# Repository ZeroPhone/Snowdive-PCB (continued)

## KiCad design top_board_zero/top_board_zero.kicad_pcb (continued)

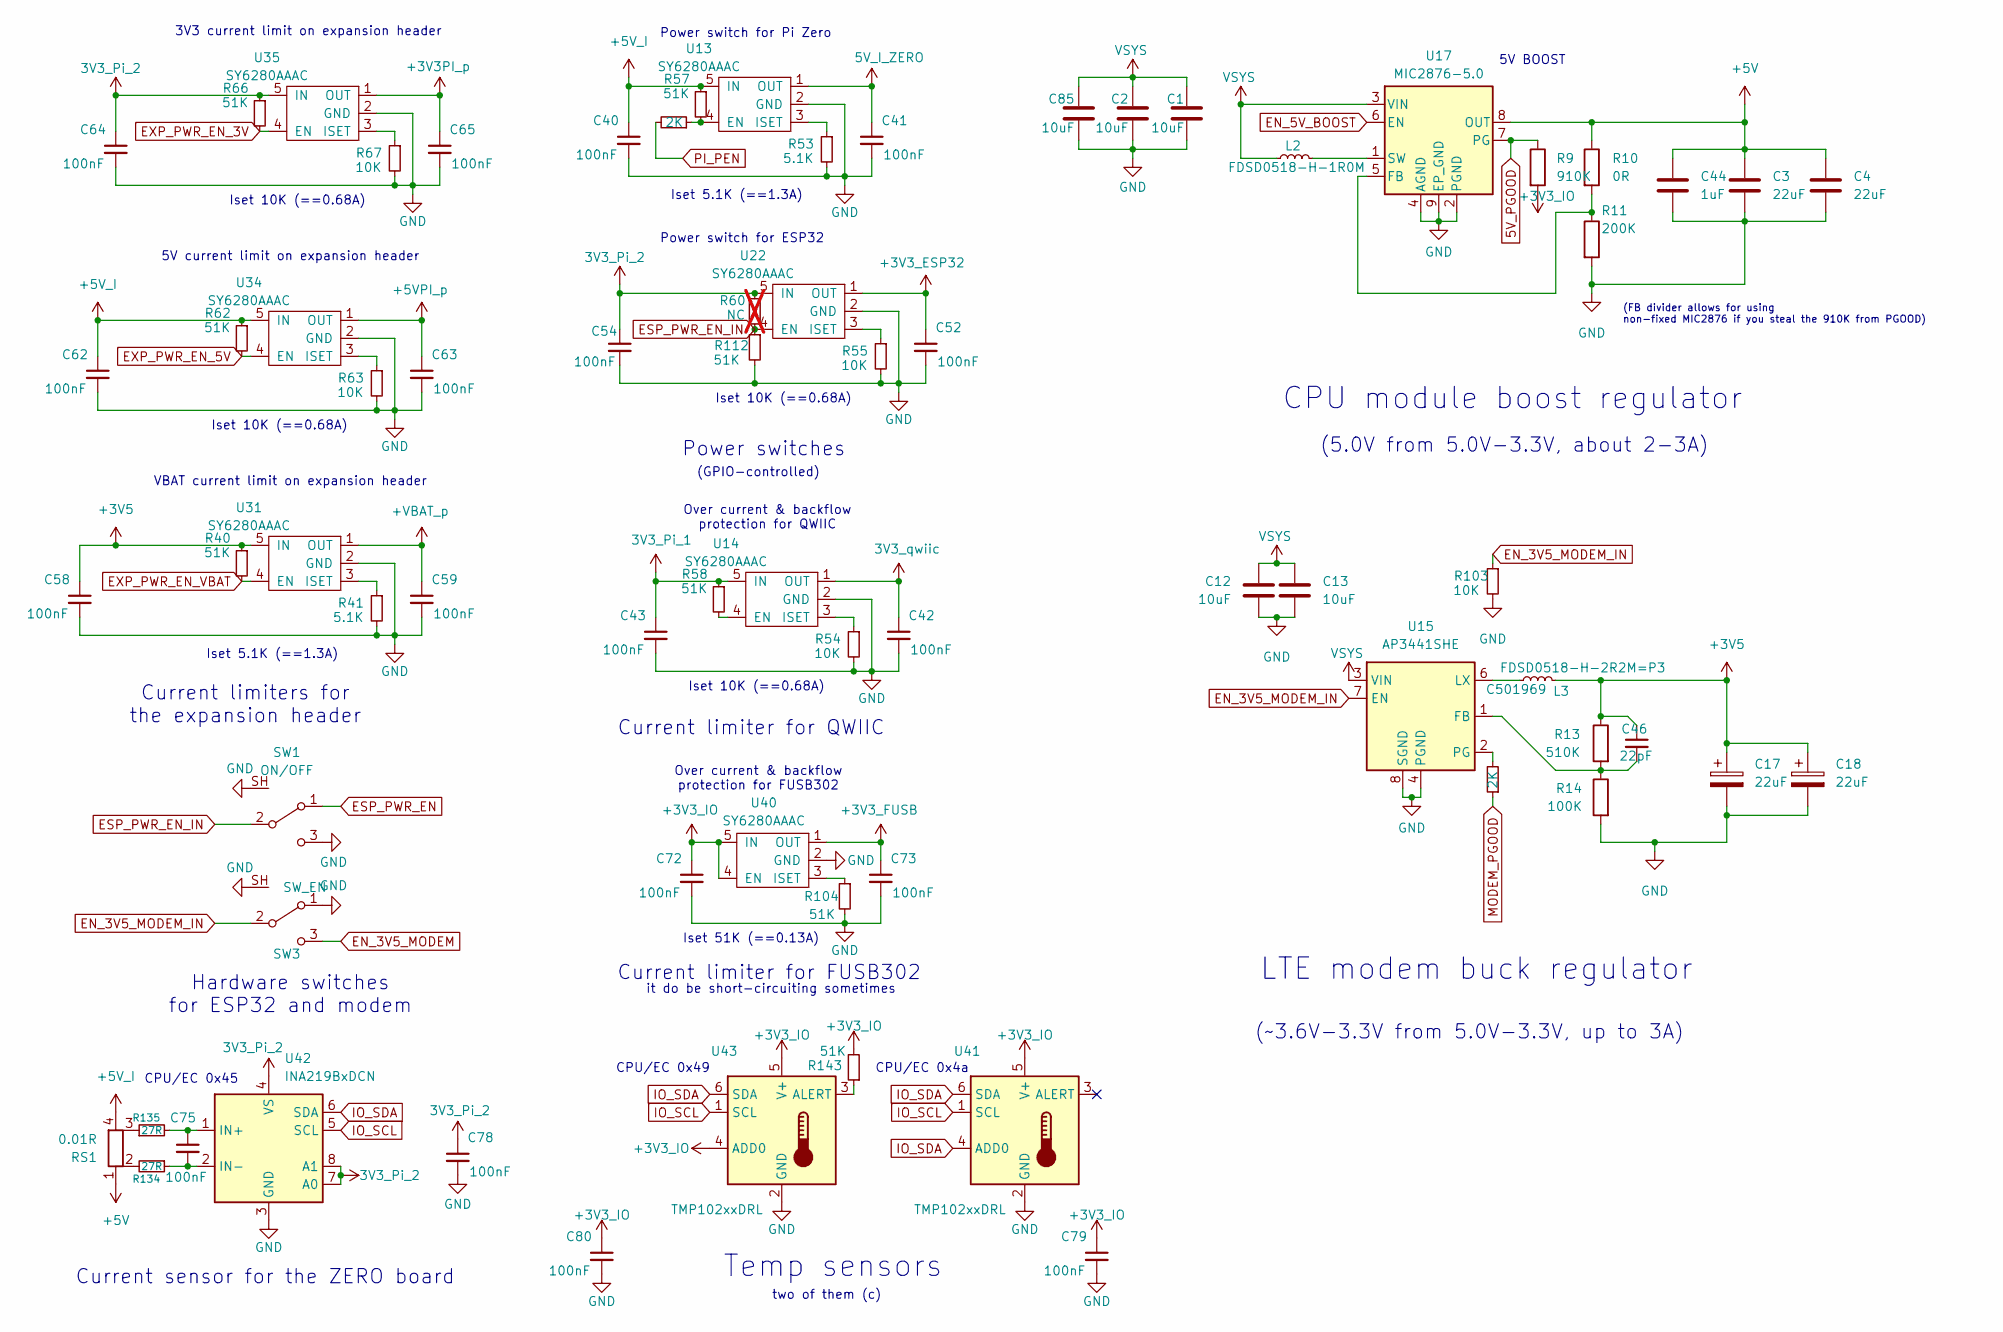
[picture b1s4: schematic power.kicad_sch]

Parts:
C1, C2, C12, C13, C85: 10uF; C_0805_2012Metric_Pad1.18x1.45mm_HandSolder
C3, C4, C17, C18: 22uF; C_0805_2012Metric_Pad1.18x1.45mm_HandSolder; LCSC Part C45783
C40, C41, C42, C43, C52, C54, C58, C59, C62, C63, C64, C65, C72, C73, C75, C78, C79, C80: 100nF; C_0402_1005Metric; LCSC Part C1525
C44: 1uF; C_0805_2012Metric_Pad1.18x1.45mm_HandSolder
C46: 22pF; C_0402_1005Metric; LCSC Part C1555
L2: FDSD0518-H-1R0M; L_Murata_FDSD0518; LCSC Part C435273
L3: FDSD0518-H-2R2M=P3; L_Murata_FDSD0518; LCSC Part C501969
R9: 910K; R_0402_1005Metric; LCSC Part C26083
R10: 0R; R_0402_1005Metric; LCSC Part C17168
R11: 200K; R_0402_1005Metric; LCSC Part C25764
R13: 510K; R_0402_1005Metric; LCSC Part C11616
R14: 100K; R_0402_1005Metric; LCSC Part C25741
R40, R57, R58, R62, R66, R104, R112, R143: 51K; R_0402_1005Metric; LCSC Part C25794
R41, R53: 5.1K; R_0402_1005Metric; LCSC Part C25905
R54, R55, R63, R67, R103: 10K; R_0402_1005Metric; LCSC Part C25744
R60: NC; R_0402_1005Metric; not fitted
R115, R116: 2K; R_0402_1005Metric; LCSC Part C4109
R134, R135: 27R; R_0402_1005Metric; LCSC Part C25105
RS1: 0.01R; Shunt; LCSC Part C175856
SW1: ON/OFF; SW_SPDT_PCM12_SH; LCSC Part C431540
SW3: SW_EN; SW_SPDT_PCM12_SH; LCSC Part C431540
U13, U14, U22, U31, U34, U35, U40: SY6280AAAC; SOT-23-5; LCSC Part C207620
U15: AP3441SHE; DFN-8-1EP_2x2mm_P0.5mm_EP0.9x1.7mm
U17: MIC2876-5.0; DFN-8-1EP_2x2mm_P0.5mm_EP0.6x1.2mm
U41, U43: TMP102xxDRL; SOT-563; LCSC Part C99269
U42: INA219BxDCN; SOT-23-8; LCSC Part C2653868

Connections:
3V3_Pi_1: C43.1, R58.1, U14.5 (IN); also elsewhere on the board
3V3_Pi_2: C54.1, C64.1, C78.1, R60.1, R66.1, U22.5 (IN), U35.5 (IN), U42.4 (VS), U42.7 (A0), U42.8 (A1); also elsewhere on the board
3V3_qwiic: C42.1, U14.1 (OUT); also elsewhere on the board
5V_I_ZERO: C41.1, U13.1 (OUT); also elsewhere on the board
5V_PGOOD: R9.1, U17.7 (PG); also elsewhere on the board
+3V3PI_p: C65.1, U35.1 (OUT); also elsewhere on the board
+3V3_ESP32: C52.1, U22.1 (OUT); also elsewhere on the board
+3V3_FUSB: C73.1, U40.1 (OUT); also elsewhere on the board
+3V3_IO: C72.1, C79.1, C80.1, R9.2, R143.2, U40.4 (EN), U40.5 (IN), U41.5 (V+), U43.4 (ADD0), U43.5 (V+); also elsewhere on the board
+3V5: C17.1, C18.1, C46.1, C58.1, L3.1, R13.1, R40.1, U31.5 (IN); also elsewhere on the board
+5V: C3.1, C4.1, C44.1, R10.1, RS1.1, U17.8 (OUT); also elsewhere on the board
+5VPI_p: C63.1, U34.1 (OUT); also elsewhere on the board
+5V_I: C40.1, C62.1, R57.1, R62.1, RS1.4, U13.5 (IN), U34.5 (IN)
+VBAT_p: C59.1, U31.1 (OUT); also elsewhere on the board
EN_3V5_MODEM: SW3.3 (C); also elsewhere on the board
EN_3V5_MODEM_IN: R103.1, SW3.2 (B), U15.7 (EN)
EN_5V_BOOST: U17.6 (EN); also elsewhere on the board
ESP_PWR_EN: SW1.1 (A); also elsewhere on the board
ESP_PWR_EN_IN: R60.2, R112.1, SW1.2 (B), U22.4 (EN)
EXP_PWR_EN_3V: R66.2, U35.4 (EN)
EXP_PWR_EN_5V: R62.2, U34.4 (EN)
EXP_PWR_EN_VBAT: R40.2, U31.4 (EN)
GND: C1.1, C2.1, C3.2, C4.2, C12.1, C13.1, C17.2, C18.2, C40.2, C41.2, C42.2, C43.2, C44.2, C52.2, C54.2, C58.2, C59.2, C62.2, C63.2, C64.2, C65.2, C72.2, C73.2, C78.2, C79.2, C80.2, C85.1, R11.2, R14.2, R41.2, R53.2, R54.2, R55.2, R63.2, R67.2, R103.2, R104.2, R112.2, SW1.3 (C), SW1.SH, SW3.1 (A), SW3.SH, U13.2 (GND), U14.2 (GND), U15.4 (PGND), U15.8 (SGND), U15.9 (SGND), U17.2 (PGND), U17.4 (AGND), U17.9 (EP_GND), U22.2 (GND), U31.2 (GND), U34.2 (GND), U35.2 (GND), U40.2 (GND), U41.2 (GND), U42.3 (GND), U43.2 (GND); also elsewhere on the board
IO_SCL: U41.1 (SCL), U42.5 (SCL), U43.1 (SCL); also elsewhere on the board
IO_SDA: U41.4 (ADD0), U41.6 (SDA), U42.6 (SDA), U43.6 (SDA); also elsewhere on the board
MODEM_PGOOD: R116.1; also elsewhere on the board
unnamed: R134.2, RS1.2
unnamed: R135.1, RS1.3
unnamed: R57.2, R115.1, U13.4 (EN)
unnamed: R53.1, U13.3 (ISET)
unnamed: R58.2, U14.4 (EN)
unnamed: R54.1, U14.3 (ISET)
unnamed: C46.2, R13.2, R14.1, U15.1 (FB)
unnamed: L3.2, U15.6 (LX)
unnamed: R116.2, U15.2 (PG)
unnamed: R10.2, R11.1, U17.5 (FB)
unnamed: L2.1, U17.1 (SW)
unnamed: R55.1, U22.3 (ISET)
unnamed: R41.1, U31.3 (ISET)
unnamed: R63.1, U34.3 (ISET)
unnamed: R67.1, U35.3 (ISET)
unnamed: R104.1, U40.3 (ISET)
unnamed: C75.1, R135.2, U42.1 (IN+)
unnamed: C75.2, R134.1, U42.2 (IN-)
unnamed: R143.1, U43.3 (ALERT)
PI_PEN: R115.2; also elsewhere on the board
VSYS: C1.2, C2.2, C12.2, C13.2, C85.2, L2.2, U15.3 (VIN), U17.3 (VIN); also elsewhere on the board

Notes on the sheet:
5V BOOST
Hardware switches for ESP32 and modem
it do be short-circuiting sometimes
Iset 10K (==0.68A)
5V current limit on expansion header
Power switch for Pi Zero
Over current & backflow protection for QWIIC
CPU/EC 0x45
two of them (c)
Power switch for ESP32
Current limiter for FUSB302
Power switches
CPU/EC 0x49
Iset 51K (==0.13A)
CPU module boost regulator
(5.0V from 5.0V-3.3V, about 2-3A)
CPU/EC 0x4a
Over current & backflow protection for FUSB302
Current limiters for the expansion header
(FB divider allows for using non-fixed MIC2876 if you steal the 910K from PGOOD)
Iset 5.1K (==1.3A)
VBAT current limit on expansion header
Temp sensors
(~3.6V-3.3V from 5.0V-3.3V, up to 3A)
Current sensor for the ZERO board
LTE modem buck regulator
3V3 current limit on expansion header
Current limiter for QWIIC
(GPIO-controlled)

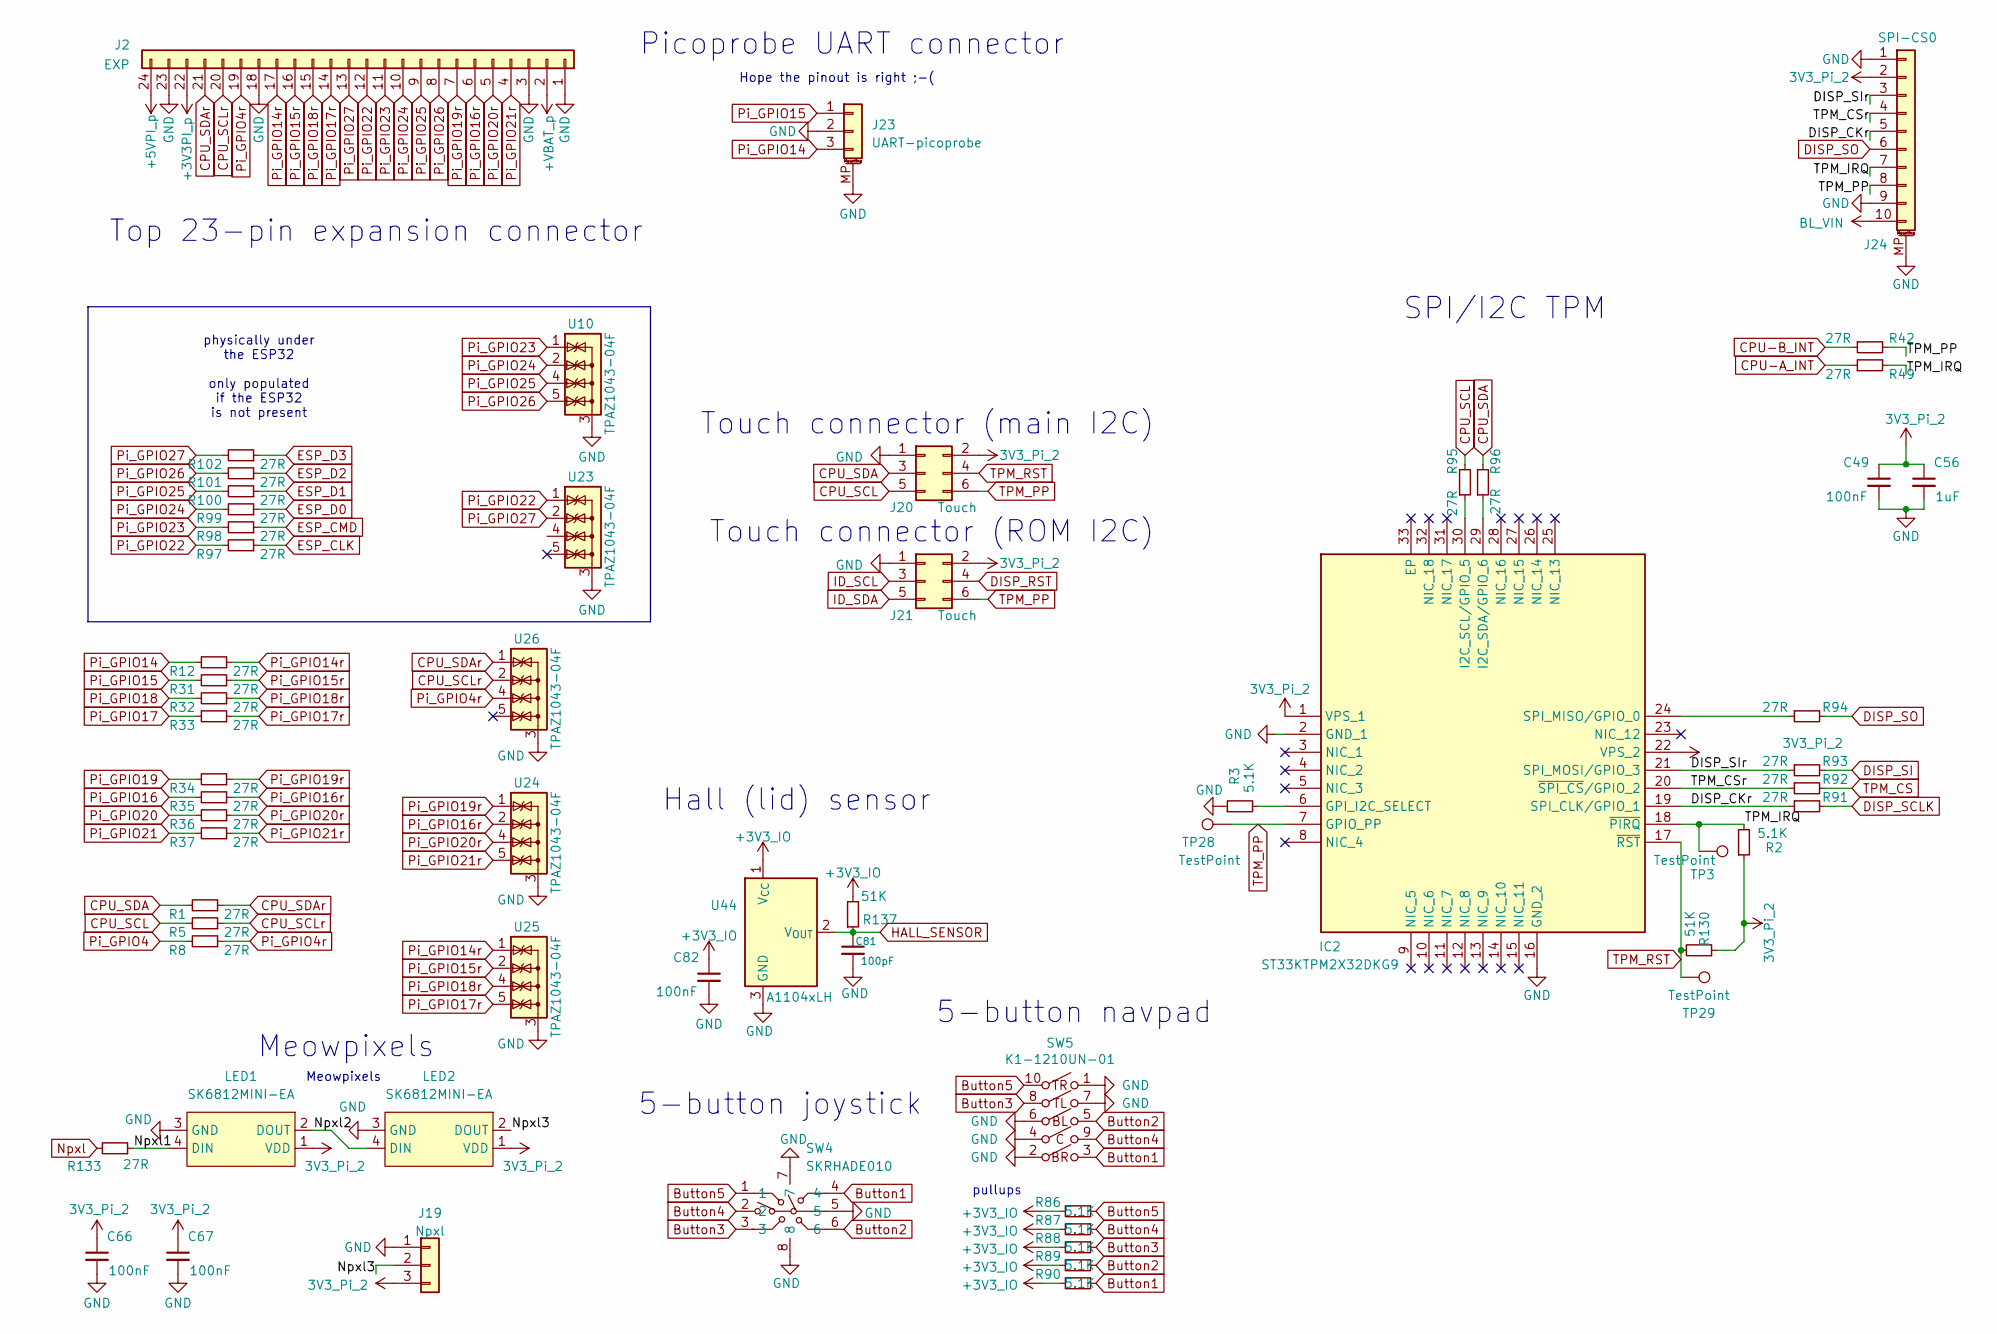
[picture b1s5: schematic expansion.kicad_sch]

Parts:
C49, C66, C67, C82: 100nF; C_0402_1005Metric; LCSC Part C1525
C56: 1uF; C_0402_1005Metric; LCSC Part C52923
C81: 100pF; C_0402_1005Metric; LCSC Part C1546
IC2: ST33KTPM2X32DKG9; QFN-32-1EP_5x5mm_P0.5mm_EP3.1x3.1mm; Manufacturer_Part_Number ST33KTPM2X32DKG9
J2: EXP; PinSocket_1x24_P2.54mm_Horizontal_SMD
J19: Npxl; PinHeader_1x03_P1.27mm_Vertical
J20, J21: Touch; PinHeader_2x03_P2.00mm_Vertical
J23: UART-picoprobe; JST_SH_SM03B-SRSS-TB_1x03-1MP_P1.00mm_Horizontal; LCSC Part C145955
J24: SPI-CS0; HRS_FH34SRJ-10S-0.5SH(50)
LED1, LED2: SK6812MINI-EA; LED-SMD_4P-L3.2-W2.8_SK6812MINI-EA; LCSC Part C5378731
R1, R5, R8, R12, R31, R32, R33, R34, R35, R36, R37, R42, R49, R91, R92, R93, R94, R95, R96, R97, R98, R99, R100, R101, R102, R133: 27R; R_0402_1005Metric; LCSC Part C25105
R2, R3, R86, R87, R88, R89, R90: 5.1K; R_0402_1005Metric; LCSC Part C25905
R130, R137: 51K; R_0402_1005Metric; LCSC Part C25794
SW4: SKRHADE010; SW-SMD_SKRHADE010; MPN SKRHADE010; LCSC Part C202415
SW5: K1-1210UN-01
TP3, TP28, TP29: TestPoint; TestPoint_Pad_D1.0mm
U10, U23, U24, U25, U26: TPAZ1043-04F; USON-10_2.5x1.0mm_P0.5mm
U44: A1104xLH; SOT-23W; LCSC Part C48935712

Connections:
3V3_Pi_2: C49.1, C56.1, C66.1, C67.1, IC2.1 (VPS_1), IC2.22 (VPS_2), J19.3, J20.2, J21.2, J24.2, LED1.1 (VDD), LED2.1 (VDD), R2.1, R130.1; also elsewhere on the board
+3V3PI_p: J2.22; also elsewhere on the board
+3V3_IO: C82.1, R86.2, R87.2, R88.2, R89.2, R90.2, R137.2, U44.1 (V_{CC}); also elsewhere on the board
+5VPI_p: J2.24; also elsewhere on the board
+VBAT_p: J2.2; also elsewhere on the board
/Expansion/DISP_CKr: IC2.19 (SPI_CLK/GPIO_1), J24.5, R91.1
/Expansion/DISP_SIr: IC2.21 (SPI_MOSI/GPIO_3), J24.3, R93.1
/Expansion/Npxl1: LED1.4 (DIN), R133.1
/Expansion/Npxl2: LED1.2 (DOUT), LED2.4 (DIN)
/Expansion/Npxl3: J19.2, LED2.2 (DOUT)
/Expansion/TPM_CSr: IC2.20 (~SPI_CS/GPIO_2), J24.4, R92.1
/Expansion/TPM_IRQ: IC2.18 (~PIRQ), J24.7, R2.2, R49.2, TP3.1 (1_1)
BL_VIN: J24.10; also elsewhere on the board
Button1: R90.1, SW4.4, SW5.3 (B); also elsewhere on the board
Button2: R89.1, SW4.6, SW5.5 (B); also elsewhere on the board
Button3: R88.1, SW4.3, SW5.8 (A); also elsewhere on the board
Button4: R87.1, SW4.2, SW5.9 (B); also elsewhere on the board
Button5: R86.1, SW4.1, SW5.10 (A); also elsewhere on the board
CPU-A_INT: R49.1; also elsewhere on the board
CPU-B_INT: R42.1; also elsewhere on the board
CPU_SCL: J20.5, R5.2, R95.2; also elsewhere on the board
CPU_SCLr: J2.20, R5.1, U26.2 (IO2), U26.9 (NC)
CPU_SDA: J20.3, R1.2, R96.2; also elsewhere on the board
CPU_SDAr: J2.21, R1.1, U26.1 (IO1), U26.10 (NC)
DISP_RST: J21.4; also elsewhere on the board
DISP_SCLK: R91.2; also elsewhere on the board
DISP_SI: R93.2; also elsewhere on the board
DISP_SO: J24.6, R94.2; also elsewhere on the board
ESP_CLK: R97.1; also elsewhere on the board
ESP_CMD: R98.1; also elsewhere on the board
ESP_D0: R99.1; also elsewhere on the board
ESP_D1: R100.1; also elsewhere on the board
ESP_D2: R101.1; also elsewhere on the board
ESP_D3: R102.1; also elsewhere on the board
GND: C49.2, C56.2, C66.2, C67.2, C81.2, C82.2, IC2.2 (GND_1), IC2.16 (GND_2), J2.1, J2.3, J2.18, J2.23, J19.1, J20.1, J21.1, J23.2, J23.MP (MountPin), J24.1, J24.9, J24.MP (MountPin), LED1.3 (GND), LED2.3 (GND), R3.1, SW4.5, SW4.7, SW4.8, SW5.1 (B), SW5.2 (A), SW5.4 (A), SW5.6 (A), SW5.7 (B), U10.3 (G), U10.8 (G), U23.3 (G), U23.8 (G), U24.3 (G), U24.8 (G), U25.3 (G), U25.8 (G), U26.3 (G), U26.8 (G), U44.3 (GND); also elsewhere on the board
HALL_SENSOR: C81.1, R137.1, U44.2 (V_{OUT}); also elsewhere on the board
ID_SCL: J21.3; also elsewhere on the board
ID_SDA: J21.5; also elsewhere on the board
unnamed: IC2.6 (GPI_I2C_SELECT), R3.2
unnamed: IC2.30 (I2C_SCL/GPIO_5), R95.1
unnamed: IC2.29 (I2C_SDA/GPIO_6), R96.1
unnamed: IC2.24 (SPI_MISO/GPIO_0), R94.1
unnamed: U23.4 (IO3), U23.7 (NC)
Npxl: R133.2; also elsewhere on the board
Pi_GPIO4: R8.2; also elsewhere on the board
Pi_GPIO4r: J2.19, R8.1, U26.4 (IO3), U26.7 (NC)
Pi_GPIO14: J23.3, R12.2; also elsewhere on the board
Pi_GPIO14r: J2.17, R12.1, U25.1 (IO1), U25.10 (NC)
Pi_GPIO15: J23.1, R31.2; also elsewhere on the board
Pi_GPIO15r: J2.16, R31.1, U25.2 (IO2), U25.9 (NC)
Pi_GPIO16: R35.2; also elsewhere on the board
Pi_GPIO16r: J2.6, R35.1, U24.2 (IO2), U24.9 (NC)
Pi_GPIO17: R33.2; also elsewhere on the board
Pi_GPIO17r: J2.14, R33.1, U25.5 (IO4), U25.6 (NC)
Pi_GPIO18: R32.2; also elsewhere on the board
Pi_GPIO18r: J2.15, R32.1, U25.4 (IO3), U25.7 (NC)
Pi_GPIO19: R34.2; also elsewhere on the board
Pi_GPIO19r: J2.7, R34.1, U24.1 (IO1), U24.10 (NC)
Pi_GPIO20: R36.2; also elsewhere on the board
Pi_GPIO20r: J2.5, R36.1, U24.4 (IO3), U24.7 (NC)
Pi_GPIO21: R37.2; also elsewhere on the board
Pi_GPIO21r: J2.4, R37.1, U24.5 (IO4), U24.6 (NC)
Pi_GPIO22: J2.12, R97.2, U23.1 (IO1), U23.10 (NC)
Pi_GPIO23: J2.11, R98.2, U10.1 (IO1), U10.10 (NC)
Pi_GPIO24: J2.10, R99.2, U10.2 (IO2), U10.9 (NC)
Pi_GPIO25: J2.9, R100.2, U10.4 (IO3), U10.7 (NC)
Pi_GPIO26: J2.8, R101.2, U10.5 (IO4), U10.6 (NC)
Pi_GPIO27: J2.13, R102.2, U23.2 (IO2), U23.9 (NC)
TPM_CS: R92.2; also elsewhere on the board
TPM_PP: IC2.7 (GPIO_PP), J20.6, J21.6, J24.8, R42.2, TP28.1 (1_1); also elsewhere on the board
TPM_RST: IC2.17 (~RST), J20.4, R130.2, TP29.1 (1_1); also elsewhere on the board

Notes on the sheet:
physically under the ESP32 only populated if the ESP32 is not present
Hall (lid) sensor
5-button joystick
Top 23-pin expansion connector
Picoprobe UART connector
Touch connector (ROM I2C)
SPI/I2C TPM
Touch connector (main I2C)
Hope the pinout is right ;-(
Meowpixels
pullups
5-button navpad

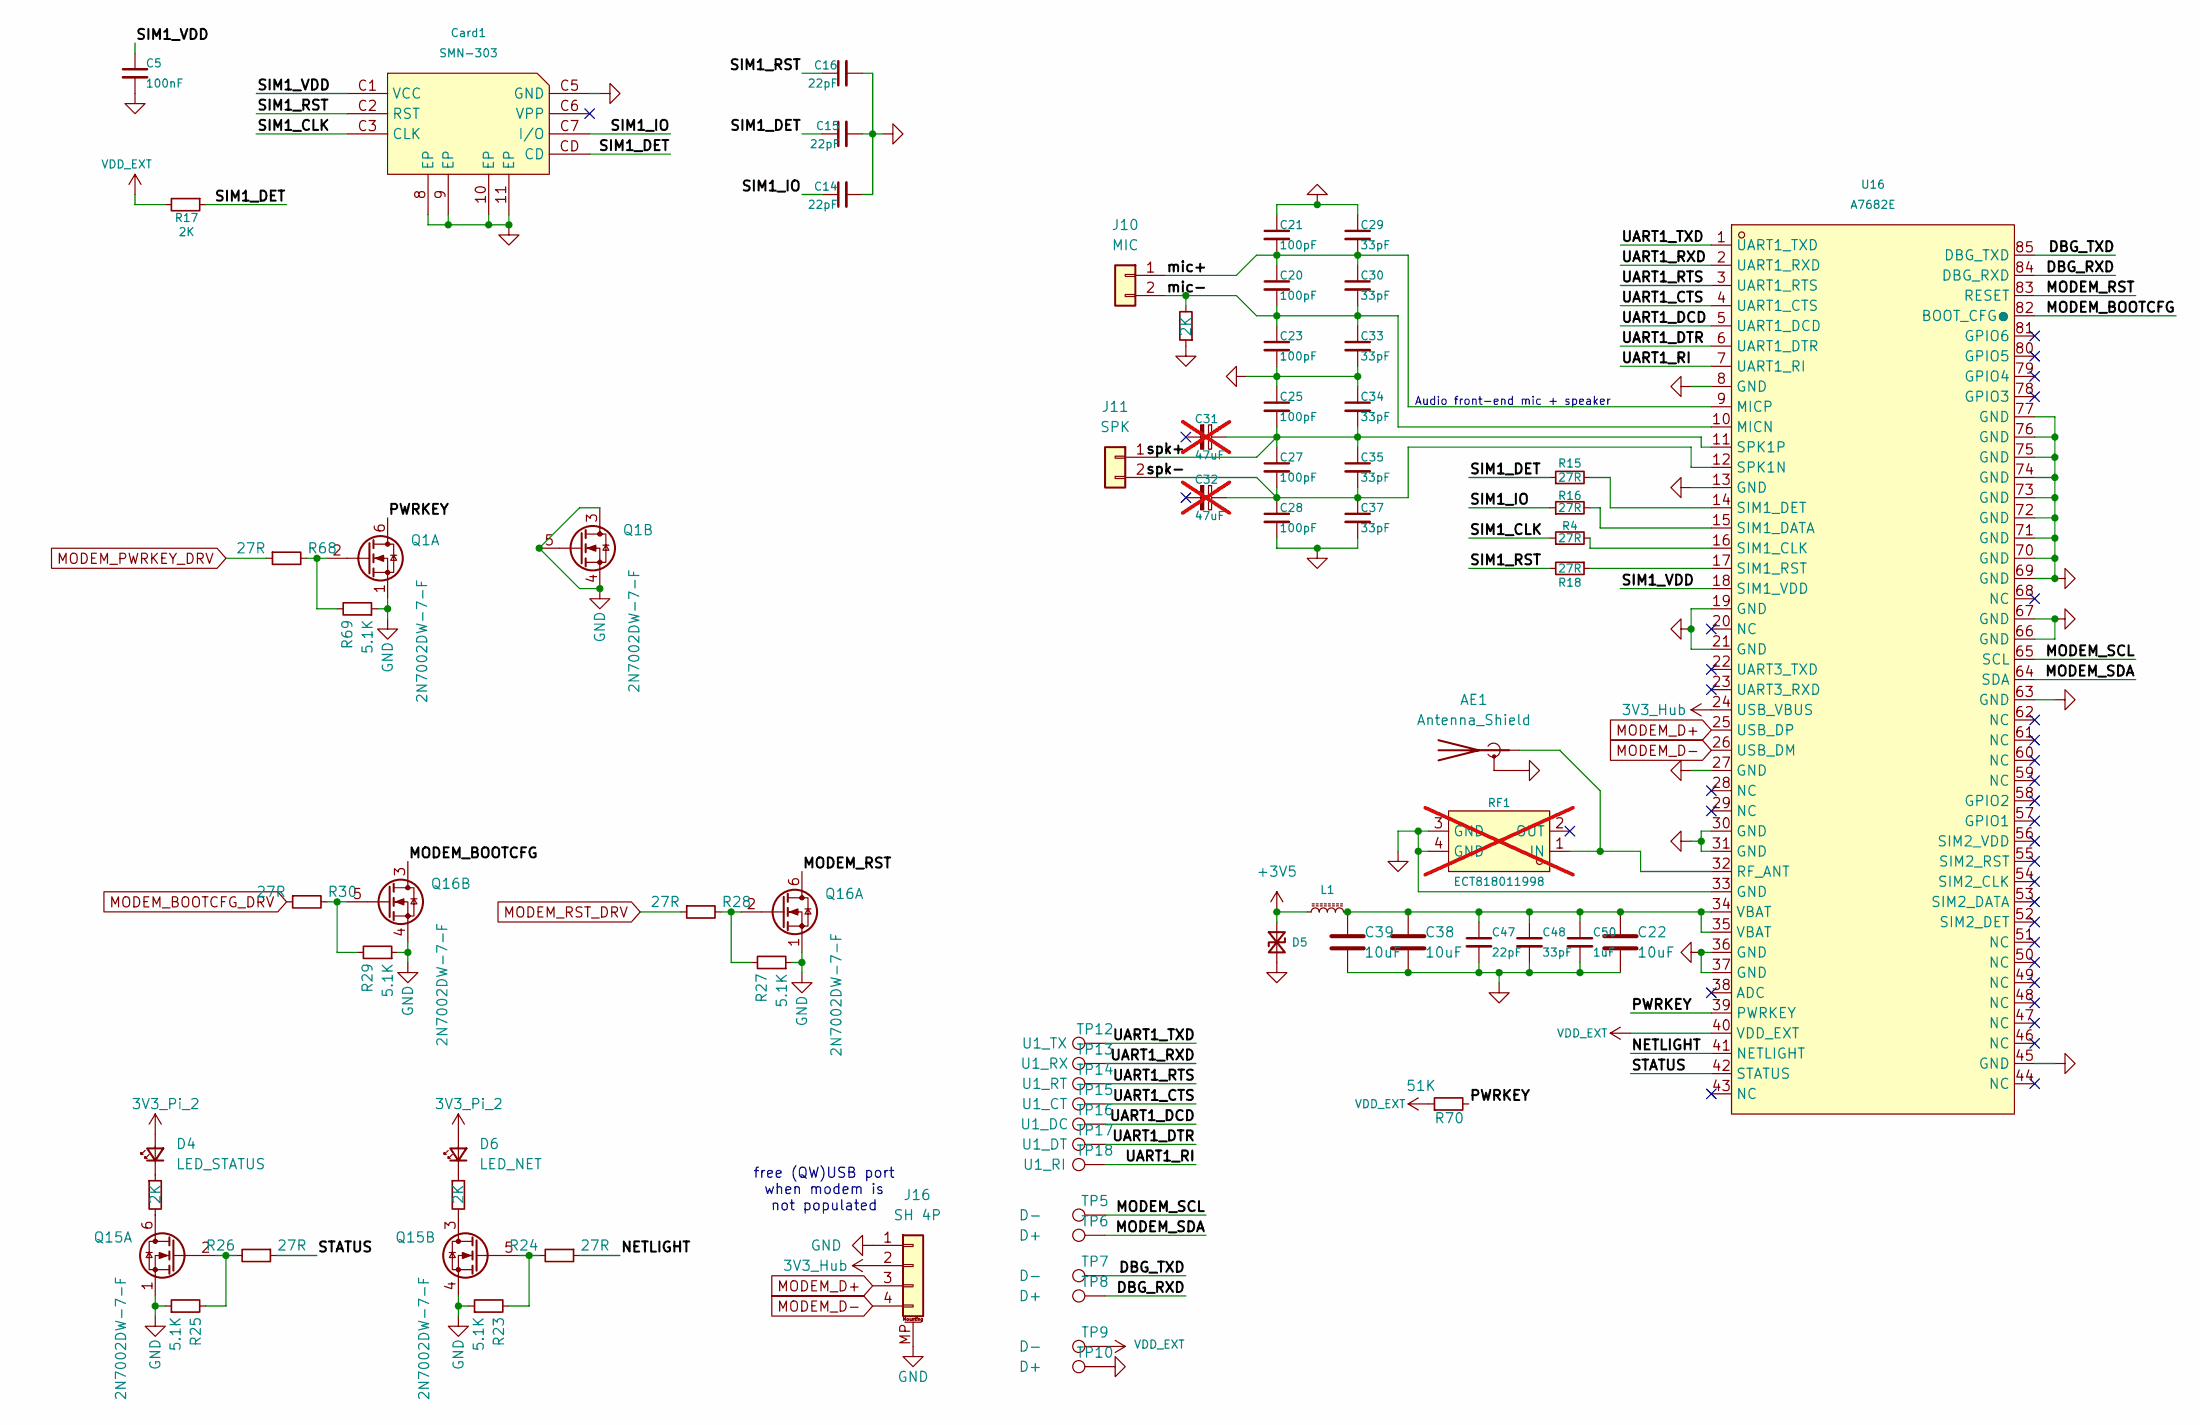
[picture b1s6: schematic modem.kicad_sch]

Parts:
AE1: Antenna_Shield; U.FL_Molex_MCRF_73412-0110_Vertical; LCSC Part C2987682
C5: 100nF; C_0402_1005Metric; LCSC Part C1525
C14, C15, C16, C47: 22pF; C_0402_1005Metric; LCSC Part C1555
C20, C21, C23, C25, C27, C28: 100pF; C_0402_1005Metric; LCSC Part C1546
C22, C38, C39: 10uF; C_0805_2012Metric_Pad1.18x1.45mm_HandSolder
C29, C30, C33, C34, C35, C37, C48: 33pF; C_0402_1005Metric; LCSC Part C1562
C31, C32: 47uF; CP_Elec_4x3.9; not fitted
C50: 1uF; C_0402_1005Metric; LCSC Part C52923
Card1: SMN-303; SIM-SMD_SMN-303; LCSC Part C266888
D4: LED_STATUS; LED_0603_1608Metric
D5: D_TVS_Small; D_0402_1005Metric_Pad0.77x0.64mm_HandSolder; LCSC Part C2441614
D6: LED_NET; LED_0603_1608Metric
J10: MIC; MICROPHONE
J11: SPK; PinHeader_1x02_P1.27mm_Vertical
J16: SH 4P; JST_SH_SM04B-SRSS-TB_1x04-1MP_P1.00mm_Horizontal; LCSC Part C970137
L1: 30Ω@100MHz 1 Line Ferrite Bead 0805 4A 14mΩ; L_0805_2012Metric; lcsc_id C16903
Q1, Q15, Q16: 2N7002DW-7-F; SOT-363_SC-70-6; LCSC Part C83571
R4, R15, R16, R18, R24, R26, R28, R30, R68: 27R; R_0402_1005Metric; LCSC Part C25105
R17, R117, R118, R136: 2K; R_0402_1005Metric; LCSC Part C4109
R23, R25, R27, R29, R69: 5.1K; R_0402_1005Metric; LCSC Part C25905
R70: 51K; R_0402_1005Metric; LCSC Part C25794
RF1: ECT818011998; IPEX-SMD_ECT818011998; LCSC Part C437250; not fitted
TP5, TP7, TP9: D-; TestPoint_Pad_1.0x1.0mm
TP6, TP8, TP10: D+; TestPoint_Pad_1.0x1.0mm
TP12: U1_TX; TestPoint_Pad_1.0x1.0mm
TP13: U1_RX; TestPoint_Pad_1.0x1.0mm
TP14: U1_RT; TestPoint_Pad_1.0x1.0mm
TP15: U1_CT; TestPoint_Pad_1.0x1.0mm
TP16: U1_DC; TestPoint_Pad_1.0x1.0mm
TP17: U1_DT; TestPoint_Pad_1.0x1.0mm
TP18: U1_RI; TestPoint_Pad_1.0x1.0mm
U16: A7682E; COMM-SMD_A7682E; LCSC Part C5362858

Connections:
3V3_Hub: J16.2, U16.24 (USB_VBUS); also elsewhere on the board
3V3_Pi_2: D4.2 (A), D6.2 (A); also elsewhere on the board
+3V5: D5.1 (A1), L1.1; also elsewhere on the board
/Modem/DBG_RXD: TP8.1 (1_1), U16.84 (DBG_RXD)
/Modem/DBG_TXD: TP7.1 (1_1), U16.85 (DBG_TXD)
/Modem/MODEM_BOOTCFG: Q16.3 (D), U16.82 (BOOT_CFG●)
/Modem/MODEM_RST: Q16.6 (D), U16.83 (RESET)
/Modem/MODEM_SCL: TP5.1 (1_1), U16.65 (SCL)
/Modem/MODEM_SDA: TP6.1 (1_1), U16.64 (SDA)
/Modem/NETLIGHT: R24.1, U16.41 (NETLIGHT)
/Modem/PWRKEY: Q1.6 (D), R70.2, U16.39 (PWRKEY)
/Modem/SIM1_CLK: Card1.C3 (CLK), R4.1
/Modem/SIM1_DET: C15.1, Card1.CD, R15.1, R17.1
/Modem/SIM1_IO: C14.1, Card1.C7 (I/O), R16.1
/Modem/SIM1_RST: C16.1, Card1.C2 (RST), R18.2
/Modem/SIM1_VDD: C5.1, Card1.C1 (VCC), U16.18 (SIM1_VDD)
/Modem/STATUS: R26.1, U16.42 (STATUS)
/Modem/UART1_CTS: TP15.1 (1_1), U16.4 (UART1_CTS)
/Modem/UART1_DCD: TP16.1 (1_1), U16.5 (UART1_DCD)
/Modem/UART1_DTR: TP17.1 (1_1), U16.6 (UART1_DTR)
/Modem/UART1_RI: TP18.1 (1_1), U16.7 (UART1_RI)
/Modem/UART1_RTS: TP14.1 (1_1), U16.3 (UART1_RTS)
/Modem/UART1_RXD: TP13.1 (1_1), U16.2 (UART1_RXD)
/Modem/UART1_TXD: TP12.1 (1_1), U16.1 (UART1_TXD)
/Modem/mic+: C20.1, C21.2, C29.2, C30.1, J10.1, U16.9 (MICP)
/Modem/mic-: C20.2, C23.1, C30.2, C33.1, J10.2, R136.2, U16.10 (MICN)
/Modem/spk+: C25.2, C27.1, C31.1, C34.2, C35.1, J11.1, U16.11 (SPK1P)
/Modem/spk-: C27.2, C28.1, C32.1, C35.2, C37.1, J11.2, U16.12 (SPK1N)
GND: AE1.2 (Shield), C5.2, C14.2, C15.2, C16.2, C21.1, C22.1, C23.2, C25.1, C28.2, C29.1, C33.2, C34.1, C37.2, C38.1, C39.1, C47.2, C48.2, C50.2, Card1.8 (EP), Card1.9 (EP), Card1.10 (EP), Card1.11 (EP), Card1.C5 (GND), D5.2 (A2), J16.1, J16.MP (MountPin), Q1.1 (S), Q1.3 (D), Q1.4 (S), Q1.5 (G), Q15.1 (S), Q15.4 (S), Q16.1 (S), Q16.4 (S), R23.1, R25.1, R27.1, R29.1, R69.1, R136.1, RF1.3 (GND), RF1.4 (GND), TP10.1 (1_1), U16.8 (GND), U16.13 (GND), U16.19 (GND), U16.21 (GND), U16.27 (GND), U16.30 (GND), U16.31 (GND), U16.33 (GND), U16.36 (GND), U16.37 (GND), U16.45 (GND), U16.63 (GND), U16.66 (GND), U16.67 (GND), U16.69 (GND), U16.70 (GND), U16.71 (GND), U16.72 (GND), U16.73 (GND), U16.74 (GND), U16.75 (GND), U16.76 (GND), U16.77 (GND); also elsewhere on the board
MODEM_BOOTCFG_DRV: R30.1; also elsewhere on the board
MODEM_D+: J16.3, U16.25 (USB_DP); also elsewhere on the board
MODEM_D-: J16.4, U16.26 (USB_DM); also elsewhere on the board
MODEM_PWRKEY_DRV: R68.1; also elsewhere on the board
MODEM_RST_DRV: R28.1; also elsewhere on the board
unnamed: AE1.1 (A), RF1.1 (IN), U16.32 (RF_ANT)
unnamed: C22.2, C38.2, C39.2, C47.1, C48.1, C50.1, L1.2, U16.34 (VBAT), U16.35 (VBAT)
unnamed: D4.1 (K), R117.1
unnamed: D6.1 (K), R118.1
unnamed: Q1.2 (G), R68.2, R69.2
unnamed: Q15.6 (D), R117.2
unnamed: Q15.2 (G), R25.2, R26.2
unnamed: Q15.3 (D), R118.2
unnamed: Q15.5 (G), R23.2, R24.2
unnamed: Q16.2 (G), R27.2, R28.2
unnamed: Q16.5 (G), R29.2, R30.2
unnamed: R4.2, U16.16 (SIM1_CLK)
unnamed: R16.2, U16.15 (SIM1_DATA)
unnamed: R15.2, U16.14 (SIM1_DET)
unnamed: R18.1, U16.17 (SIM1_RST)
VDD_EXT: R17.2, R70.1, TP9.1 (1_1), U16.40 (VDD_EXT)

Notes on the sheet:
free (QW)USB port when modem is not populated
Audio front-end mic + speaker
